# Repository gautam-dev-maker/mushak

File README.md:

# About The Project

Mushak is a micromouse maze solving bot. The aim of this project is to make India's first and smallest half-size micromouse bot. "Mushak" in hindi means "Mouse".

This micromouse consist of a very small coreless motors (6 mm width and 10 mm length) and PCB as it's base . Since coreless motors doesn't provide enough torque for the movements of bot we used gear box to increase the torque.

Mushak is of size 45.7mm x 40.0 mm, which is smaller than similar micromouse using STM32F405RG. We boast of least area consuming micromouse made using STM32 LQFP64 package chips.

|             |  |
:-------------------------:|:-------------------------:

# Table of Content
- [About The Project](#about-the-project)
- [Table of Content](#table-of-content)
- [File Structure](#file-structure)
- [PCB Design](#pcb-design)
    - [Major components used in the PCB include -](#major-components-used-in-the-pcb-include--)
  - [IR sensors](#ir-sensors)
    - [Placement of IR Sensors](#placement-of-ir-sensors)
  - [Power Distribution](#power-distribution)
  - [STM32F405RG (Microcontroller)](#stm32f405rg-microcontroller)
  - [DRV8833 (Motor Driver)](#drv8833-motor-driver)
  - [VL6180X (ToF Sensor)](#vl6180x-tof-sensor)
  - [HC-08 (BLE Module)](#hc-08-ble-module)
  - [AS5600 (Magnetic Encoder)](#as5600-magnetic-encoder)
  - [MPU6500 (IMU)](#mpu6500-imu)
  - [Routing](#routing)
  - [Solutions to some of the major problems faced while designing PCB](#solutions-to-some-of-the-major-problems-faced-while-designing-pcb)
- [CAD Design](#cad-design)
  - [Part Descriptions](#part-descriptions)
  - [Issues Faced in Mechanical Designing](#issues-faced-in-mechanical-designing)
    - [Designing Mount](#designing-mount)
    - [Finalising and Meshing the gears](#finalising-and-meshing-the-gears)
- [Firmware](#firmware)
  - [File Structure](#file-structure-1)
  - [Pinout of STM32F405RG](#pinout-of-stm32f405rg)
    - [Communication Buses](#communication-buses)
    - [ADC](#adc)
    - [PWM](#pwm)
    - [GPIO](#gpio)
  - [How To Use The Firmware](#how-to-use-the-firmware)
    - [Install gcc-arm-none-eabi compiler tool suite](#install-gcc-arm-none-eabi-compiler-tool-suite)
    - [Install ST-Link Toolchain](#install-st-link-toolchain)
    - [Build the source code](#build-the-source-code)
    - [Flash on the STM32 device](#flash-on-the-stm32-device)
- [Resources](#resources)
- [Acknowledgements](#acknowledgements)
- [License](#license)

# File Structure

    .
    ├── Assets             # Documentation files screenshots, gifs, videos of results
    ├── firmware           # contains required code for controlling the bot
    ├── pcb_design         # PCB files made in  kicad 6
    ├── cad_design         # CAD files of mushak (micromouse)
    ├── LICENSE            # License for this project
    └── README.md          # Contains documentation and information about this project

Further file structure of each folder is given in below sections.

# PCB Design

The Mushak PCB design is made on the latest version of KiCAD 6.

Mushak is designed over STM32F405RG microcontroller accomodated with various sensors and drivers for the micromouse.

We designed the smallest micromouse that is based on STM32F405RG microcontroller

### Major components used in the PCB include -

|     Components        |          Description          |
| --------------------- | ----------------------------- |
| STM32F405RG           | Microcontroller |
| VL6180x | ToF sensor4 |
| DRV8833 | Motor Driver |
| MPU6500 | IMU |
| SFH-4045N | Infrared Emitter |
| SFH-3015-FA | Phototransistor (Reciever) |

---

## IR sensors

* The IR sensors include majorly two components, IR emitter which emits the Infrared light of a particular wavelength which is not visible with the human eye. 

* This light gets reflected back from the obstacle present in form of the robot to the photo transistor, when the Infrared light of this perticular wavelength enters the phototransistor device it allows the current to flow from the collector to the emmiter of device. This current flow creates a voltage drop across the resistor connected with the photo transistor and this voltage drop is read by th ADC of the microcontroller which varies as the intensity of light reflected changes. By this way we can determine how far is the obstacle from the robot.

* For controlling the intensity of the transmitted light we used N-Channel Mosfet whose gate is controlled by PWM signal given by the microcontroller.
By varying the PWM duty cycle we can control the intensity of the transmitted light from IR emmiter by which we can control the distance sensitivity.

* Four Sensor pairs are being used in Mushak (Micromouse)

### Placement of IR Sensors

Placing IR sensors pose a challenge, and required rigorous testing and brain storming. 

As can be seen in the image above we have visualised 2 cell based maze and bot is placed in first cell.

* `IR1` (blue rays) is pointing to the left mid point of next cell.
* `IR2` (orange rays) is pointing to the left end of current cell.
* `IR3` (pink rays) is pointing to the right end of current cell.
* `IR4` (green rays) is pointing to the right end of current cell.

To move the bot in straight line along the diagonal maze pattern , we have considered `point 1` and `point 2`. These two points are the edges of diagonal ends of above pattern . So if bot had to move diagonally we can check for readings at these two points and control the bot accordingly.

---

## Power Distribution
* Power to the control circuits is provided by 3V linear Regulator(LDO) which can provide upto 1A current. Power to the motor is directly given to the motor driver through battery.
* Additional capacitors are added across outputs for filtering out the voltage. Voltage divider resistors are being used to monitor the battery voltage. Power indication LED has been provided in the PCB. The input voltage for the PCB is 3.7 voltage through a general LiPo battery.

--- 

## STM32F405RG (Microcontroller)

The below image shows the pinout of STM32F405RG that we will be using for this project :

Decoupling capacitors of 0.1uF are connected near the vdd pins of STM32. Additional external low and high frequency oscillators are added for precise timing.

- HSE(High Speed External) clock - 25 Mhz
- LSE(Low Speed External) clock - 32.769 Khz

Filter circuit is being used for filtering out the analog reference voltage. Additional Debug switches are being added for debugging purposes

---
## DRV8833 (Motor Driver)

* We have used H-bridge motor driver which can control two motors at the same time via PWM (pulse width modulation) from the STM32F405RG (microcontroller).

* The motor driver can supply 1.5 Amps of current per motor which is enough to power up the coreless motors. 

* This motor driver keeps the controls terminals from the microcontrolller isolated from noise and high volatages of the motor power supply.

---

## VL6180X (ToF Sensor)

* We added a Time of Flight sensor in front of the robot to measure the distance of the obstacle in front from the robot.

* This sensor measures the time taken by the light signal to get reflected from the obstacle and then measures the distace of the obstacle from the robot.

* The sensor uses I2C protocol for communication with the microcontroller and send the distance values. It also has an additional feature of sensing the ambeint light which we can use to avoid the problems faced with IR sensors due to varing ambient light conditions.
* Due to cost issues it is not feasible to replace IR sensors with VL6180x, else it could have been a replacement.

---

## HC-08 (BLE Module)

* We used a BLE(Bluetooth Low Energy) module to communicate to the robot. It is one of the most important modules that is being used in mushak, this bluetooth module will enable us to communicate with the robot and precisely tune it to solve the mazes, additionally it makes debugging easier for us making Mushak user friendly.

* The module consumes very less power(since it works on BLE) and works on UART communication to talk with the microcontroller.

* For attaching this module we have provided the JST connectors to connect this module externally when required.

---

## AS5600 (Magnetic Encoder)

* To measure the RPM and the distance that the robot has covered we needed a type of encoder feedback. For this we used AS5600 magnetic encoders to measure the amount of rotation of the robot wheel.

* The magnetic encoders are mounted in an innovative way due to which no external mounts were required for their placement. Since magnets need to be right infront of the IC of AS5600 to get proper reading, we have taken extra care with mount size and shaft placement.

* The sensor works on I2C communication protocol to provide the reading to the microcontroller.

---

## MPU6500 (IMU)

* This sensor gives the feedback of orientaion of the robot. This MEMS based chip has in-built Acclereometer and Gyroscope by which it can determine its orietation with respect to space.

* This sensor works on SPI as well as I2C communication protocol but in our case to get the fastest data transfer, we used use SPI communcation.

---

## Routing

* Front Copper Layer:

* Back Copper Layer:

* Final Routing:

For routing of the control circuitry we used traces of 0.2mm width and for power connections we used 0.4mm width tracks to ensure fairly high current flow.

## Solutions to some of the major problems faced while designing PCB

1) Minimalising passive components is a really hard task. So to solve this I properly reffered the application notes and datasheet of stm32f405RG. Moreover the design is well tested on simulation platform.

2) Efficient placement of components to reduce the size of the PCB. Innovative design to fix sensors and encoders in such a small space.

3) Since IRs are sensitive to ambient light we required a mechanism to adjust the brighness of IR Emitter. So to do that we used a mosfet based circuit, so brightness can be controlled using PWM.

4) It was a big challenge to place 90+ SMD and THT components on a small size PCB of just 45.7x40mm size.

# CAD Design

CAD design consist of 3D modeling of Bot design.Before design can be made on PCB, we need to check if various other aspects of systems and mechanical design satisfy our requiements. So CAD design form a very important part of our project.

## Part Descriptions
* The bot contains a total of 6 main **mechanical** components which are as listed in the following table :

|     Parts             |          Description          |
| --------------------- | ----------------------------- |
| <p align="center">
   | Motors - This motor has </br> dimensions: Length x Dia. 12 x 6 mm and a shaft lenght of 6mm.|
   | Motor_mount - This is the mount for the motors, which holds </br> the motor, shaft, gears, bearing and magnet.Because of less center-to-center distance between gears, after many iterations this mount was designed.|
   | TOF_mount - This is the mount for TOF sensor, which is placed </br> in front. We have used VL6180x TOF sensor.|  
    | IR_mounts - These are the mounts for IR sensors placed </br> at specific angles. SFH-3015-FA and SFH-4045N sensors are phototransistors and IR emitters respectively.|   
    | Gears - The metal gears were extracted from mg90s servos having dimensions: </br> Driving gear:</br> &emsp; &emsp; &emsp;&emsp; &emsp;Teeth 9 </br> &emsp; &emsp; &emsp;&emsp; &emsp;Pressure Angle - 20º</br> &emsp; &emsp; &emsp;&emsp; &emsp;ID - 0.5, OD - 2.14 mm</br> &emsp; &emsp; &emsp;&emsp; &emsp;Width 2.46 mm</br> Driven gear: </br> &emsp; &emsp; &emsp;&emsp; &emsp;Teeth 47 </br> &emsp; &emsp; &emsp;&emsp; &emsp;Pressure Angle 20º</br> &emsp; &emsp; &emsp;&emsp; &emsp;ID - 1.5mm, OD - 9.55 mm</br> &emsp; &emsp; &emsp;&emsp; &emsp; Width 1.2 mm.</br> Center to center distance is 5.80mm and modulus 0.195</br>| 
    | Bearings, shaft and Wheels - These are the passive components used.</br> Bearings x4 of dimensions: ID x OD 1.5 x 4 mm.</br> Shaft x2 of dimensions: Length x Dia. 15 x 1.5 mm.</br> Wheels with dimensions: ID x OD 1.5 x 12.5 mm.</br> A combination of 2 bearings is used to house the shaft for better stability and lesser Vibrations.|
</p>

**NOTE** : 
* ID is abbreviation for Internal Diameter.
* OD is abbreviation for Outer Diameter.

## Issues Faced in Mechanical Designing 
### Designing Mount 
  
* **Issue** : The main issues faced in designing the Mount were As the Gears acquired were of a smaller diameter, there was an issue of interference between the bearing and the motor. As they were too close, it was impossible to 3D print a mount with the thickness less than 1mm.
* **Solution** : The solution opted for this was to actually disalign the motor and the shaft to give room the bearing housing to be 3D printed. This enabled us to print a more stable base due to the stronger Shaft housing.
Below images demonstrate how it was done.

|             |  |  |  |
:-------------------------:|:-------------------------:|:-------------------------:|:-------------------------:
  
### Finalising and Meshing the gears
  
* **Issue** : As there are a varieties of gears available. It was hard for us to choose the right combination and Built the Model and mounts around it.
* **Solution** : We started with finalising the sizes and the gear ratios needed according to the available spaces. We then did the market research to find the gears closest to our needs and incorporated those models into the Design.

<p align="center">

# Firmware

The firmware for this project is written using STM32-HAL. STM32 HAL consist of bare-metal register address and light weight peripheral libraries giving programmer the full control. For running multiple tasks we are using [FreeRTOS](https://www.freertos.org). We will be storing the maze in flash memory, since page size is 2 bytes, we need to access 2 bytes at a a time. 

The firmware is required to interact with the following external sensors/peripherals: 

- [SFH-4045N](https://dammedia.osram.info/media/resource/hires/osram-dam-2496064/SFH%204045N.pdf) : Infrared Emitter for detecting walls.
- [SFH-3015-FA](https://dammedia.osram.info/media/resource/hires/osram-dam-2495986/SFH%203015%20FA.pdf) : Infrared Receiver to receive the emitted 
- [AS5600-ASOT](https://ams.com/documents/20143/36005/AS5600_DS000365_5-00.pdf) : Encoders to calculate the movements of wheel.
- [DRV8833](https://www.ti.com/lit/ds/slvsar1e/slvsar1e.pdf?ts=1661677330657&ref_url=https%253A%252F%252Fwww.google.com%252F) : Dual H-bridge Motor driver required to control motor.
- [MPU6500](https://invensense.tdk.com/wp-content/uploads/2020/06/PS-MPU-6500A-01-v1.3.pdf) : Gyroscope and Accelerometer sensor.
- [SMT-0440-S-R](https://www.puiaudio.com/media/SpecSheet/SMT-0440-S-R.pdf) : buzzer to generate the victory sound.
- [VL6180x](https://www.st.com/resource/en/datasheet/vl6180x.pdf) : Time of flight sensor to measure the distance between wall and bot.
- [HC-08](http://www.hc01.com/downloads/HC-08A%20version%20english%20datasheet.pdf) : Bluetooth module primarily used for logging. It uses 9600 baud rate for communication.

## File Structure

    .
    ├── Firmware                                # contains required code for controlling the bot
    │    ├── Core                               # Contains developer code for sensors and other peripherals
    │    │   ├── As5600                         # Driver Api for AS5600
    │    │   │   ├── as5600.c                   # Source code for AS5600
    │    │   │   └── as5600.h                   # Header file for AS5600
    │    │   ├── Ble_logger                     # Bluetooth logger API using UART
    │    │   │   ├── ble_logger.c               # Bluetooth logger source code
    │    │   │   └── ble_logger.h               # Bluetooth logger header file
    │    │   ├── Drv8833                        # Code for Motor Control
    │    │   │   ├── drv8833.c                  # Source code for DRV8833
    │    │   │   └── drv8833.h                  # Header files for DRV8833
    │    │   ├── Inc                  
    │    │   │   ├── FreeRTOSConfig.h           # FreeRTOS configuration file
    │    │   │   ├── main.h                     # Main header file
    │    │   │   ├── stm32f4xx_hal_conf.h       # STM32 HAL configuration file
    │    │   │   └── stm32f4xx_it.h             # contains header of interrupt handlers
    │    │   ├── Mpu6500
    │    │   │   ├── mpu6500.c                  # Source code for MPU6500 Driver
    │    │   │   └── mpu6500.h                  # Header file for MPU6500 Driver
    │    │   ├── Peripheral                     
    │    │   │   └── I2c                        # I2C API's handler
    │    │   ├── Src
    │    │   │   ├── freertos.c                 # FreeRTOS source code
    │    │   │   ├── main.c                     # Main source code
    │    │   │   ├── stm32f4xx_hal_msp.c        # MSP initialisation and deinitialiation source code
    │    │   │   ├── stm32f4xx_it.c             # source code for interrupt handlers
    │    │   │   └── system_stm32f4xx.c         # CSMSIS peripheral device layer source code
    │    │   └── Vl6180x
    │    │       ├── vl6180x.c                  # VL6180x Driver source code
    │    │       └── vl6180x.h                  # VL6180x header file
    │    ├── Drivers                            # STM32 Driver Code involving bare metal registers
    │    ├── Middlewares                        # FreeRTOS APIs for scheduling algorithm
    │    ├── node_modules                       # HTML modules for viewing STM32 HAL API documentation
    │    ├── Makefile                           # Automake compilation instructions
    │    ├── STM32F411CEUx_FLASH.ld             # Linker script for compilation   
    └────└── node_modules                       # HTML modules for viewing STM32 HAL API

## Pinout of STM32F405RG

The below image shows the pinout of STM32F405RG that we will be using for this project :

### Communication Buses

- **I2C (Inter-Integrated Circuit)** : We use two encoders(*AS5600*),so we needed to use two different I2C bus. *Vl6180x* (ToF) sensor also uses I2C bus communication, so overall 3 I2C bus communication is used.
- **SPI (serial peripheral interface)** : *MPU6500* supports both I2C as well as SPI, but since SPI offers faster communication , we decided to go with it.
- **UART (Universal Asynchronous Receiver/Transmitter)**: *HC-08* bluetooth module , which will be used for logging functions on UART transmission protocol.

### ADC

- SFH-3015-FA (IR receiver) gives analog signals, so it requires ADC module to read the readings. So we require 4 ADC channels for reading IR sensors
- To measure voltage level of battery one ADC channel will be required

So overall 5 ADC channels are required.

### PWM

- DRV8833 (Dual H-bridge Motor Driver) requires 4 PWM channel.
- To control the brightness of 4 SFH-4045N (IR emitter) we need 4 more PWM channels
- To generate noise in the buzzer we will need 1 more PWM channel.

So in overall we will require 9 PWM channels.

### GPIO

- 2 GPIOs are required for 2 LEDs
- 1 GPIOs are required for 1 Button

so In overall 3 GPIO pins are used for getting input and output.

## How To Use The Firmware

### Install gcc-arm-none-eabi compiler tool suite

* ### For Linux 

```
sudo apt-get update
sudo apt-get install -y gcc-arm-none-eabi
```

* ### For MacOS
```
brew tap ArmMbed/homebrew-formulae
brew install arm-none-eabi-gcc
```
### Install ST-Link Toolchain

* ST-Link toolchain is required for flashing on STM32 chip.

* ### For Linux
```
sudo apt-get update
sudo apt-get -y install stlink-tools
```

* ### For MacOS

```
brew install stlink
```

### Build the source code

* ### Clone the reponsitory and change the directory to firmware

```
git clone https://github.com/gautam-dev-maker/mushak.git
cd mushak/firmware
```

* ### Build using make tool
```
make -j4  # based on no. of logical cores available in your system
```

### Flash on the STM32 device

```
make flash  # Currently only st-link support is added
```

# Resources
* [Project Futura](http://micromouseusa.com/?page_id=1342) is a tutorial for micromouse designing
* [Micromouse Tyre](http://micromouseusa.com/?page_id=1342) a blog related how to select the tyres for micromouse
* [Phase-lead controller](https://micromouseonline.com/2011/05/16/designing-a-phase-lead-controller/) an alternative to PID control systems for micromouse.
* [Slip Compensation](https://robotics.stackexchange.com/questions/1658/implementing-slip-compensation-into-a-half-size-micromouse) discussion on how to compensate slip in micromouse which becomes a serious issue
* [Kerise v5](https://github.com/kerikun11/micromouse-kerise-v5) Smallest micromouse ever made, contains good documentation of design,pcb and code.
* [SolidWorks Tutorial](https://www.youtube.com/watch?v=Ulttc_2p4DY&list=PLrOFa8sDv6jcp8E3ayUFZ4iNI8uuPjXHe) to sharpen your skills in SolidWorks.

# Acknowledgements
* [SRA VJTI](http://sravjti.in) for providing us with required resources and support.
* [Ryotaro Onuki](https://github.com/kerikun11) for helping with all the designs and technical aspect of micromouse. His willingness to share his experience and answering our question has led to the start of the project.

# License
The [License](https://github.com/gautam-dev-maker/mushak/blob/master/LICENSE) Used for this Project.

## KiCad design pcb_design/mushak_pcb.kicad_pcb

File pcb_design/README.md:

# PCB Design

The Mushak PCB design is made on the latest version of KiCAD 6.

Mushak is designed over STM32F405RG microcontroller accomodated eith various sensors and drivers for the micromouse.

We designed the smallest micromouse that is based on STM32F405RG microcontroller

### Major components used in the PCB include -

- STM32F405RG - Microcontroller
- VL6180x - ToF sensor4
- DRV8833 - Motor Driver
- MPU6500 - IMU
- SFH-4045N - Infrared Emitter
- SFH-3015-FA - Phototransistor (Reciever)

---

## IR sensors

The IR sensors include majorly two components, IR emitter which emits the Infrared light of a perticular wavelength which is not visible with the human eye. 

This light gets reflected back from the obstacle present in fromt of the robot to the photo transistor, when the Infrared light of this perticular wavelength enters the phototransistor device it allows the current to flow from the collector to the emmiter of device. This current flow creates a voltage drop across the resistor connected with the photo transistor and this voltage drop is read by th ADC of the microcontroller which varies as the intensity of light reflected changes. By this way we can determine how far is the obstacle from the robot.

For controlling the intensity of the transmitted light we used N-Channel Mosfet whose gate is controlled by PWM signal given by the microcontroller.
By varying the PWM duty cycle we can control the intensity of the transmitted light from IR emmiter by which we can control the distance sensitivity.

4 Sensor pairs are being used in Mushak (Micromouse)

---

## Power Distribution
Power to the control circuits is provided by 3V linear Regulator(LDO) which can provide upto 1A current. Power to the motor is directly given to the motor driver through battery.
Additional capacitors are added across outputs for filtering out the voltage. Voltage divider resistors are being used to monitor the battery voltage. Power indication LED has been provided in the PCB. The input voltage for the PCB is 3.7 voltage through a general LiPo battery.

--- 

## STM32F405RG (Microcontroller)

The below image shows the pinout of STM32F405RG that we will be using for this project :

Decoupling capacitors of 0.1uF are connected near the vdd pins of STM32. Additional external low and high frequency oscillators are added for precise timing.

- HSE(High Speed External) clock - 25 Mhz
- LSE(Low Speed External) clock - 32.769 Khz

Filter circuit is being used for filtering out the analog reference voltage. Additional Debug switches are being added for debugging purposes

---
## DRV8833 (Motor Driver)

We have used H-bridge motor driver which can control two motors at the same time via PWM (pulse width modulation) from the STM32F405RG (microcontroller).

The motor driver can supply 1.5 Amps of current per motor which is enough to power up the coreless motors. 

This motor driver keeps the controls terminals from the microcontrolller isolated from noise and high volatages of the motor power supply.

---

## VL6180X (ToF Sensor)

We added a Time of Flight sensor in front of the robot to measure the distance of the obstacle in front from the robot.

This sensor measures the time taken by the light signal to get reflected from the obstacle and then measures the distace of the obstacle from the robot.

The sensor uses I2C protocol for communication with the microcontroller and send the distance values. It also has an additional feature of sensing the ambeint light which we can use to avoid the problems faced with IR sensors due to varing ambient light conditions.

---

## HC-08 (BLE Module)

We used a BLE(Bluetooth Low Energy) module to talk to the robot. It is one of the most important modules that is being used in mushak, this bluetooth module will eanble us to talk with the robot and precisely tune it to solve the mazes, additionally it makes debugging easier for us making Mushak user friendly.

The module consumes very less power and works on UART communication to talk with the microcontroller.

For attaching this module we have provided the JST connectors to connect this module externally when required.

---

## AS5600 (Magnetic Encoder)

To measure the RPM and teh distance that the robot has covered we needed a type of encoder feedback. For this we used AS5600 magnetic encoders to measure the amount of rotation of the robot wheel.

The magnetic encoders are mounted in an innovative way due to which no external mounts were required for their placement.

The sensor works on I2C communication protocol to provide the feedback to the microcontroller.

---

## MPU6500 (IMU)

This sensor gives the feedback of orientaion of the robot. This MEMS based chip has in-built Acclereometer and Gyroscope by which it can determine its orietation with respect to space.

This sensor works on SPI as well as I2C communication protocol but in our case to get the fastest data transfer, we used use SPI communcation.

---

## Routing

Front Copper Layer:

Back Copper Layer:

Final Routing:

For routing of the control circuitry we used traces of 0.2mm width and for power connections we used 0.4mm width tracks to ensure fairly high current flow.

These are some images of the routing done on Mushak -
## Solutions to some of the major problems faced while designing PCB

1) Minimalising passive components is a really hard task. So to solve this I properly reffered the application notes and datasheet of stm32f405RG. Moreover the design is well tested on simulation platform.

2) Efficient placement of components to reduce the size of the PCB. Innovative design to fix sensors and encoders in such a small space.

3) Since IRs are sensitive to ambient light we required a mechanism to adjust the brighness of IR Emitter. So to do that we used a mosfet based circuit, so brightness can be controlled using PWM.

4) It was a big challenge to place 90+ SMD and THT components on a small size PCB of just 45.7x40mm size.

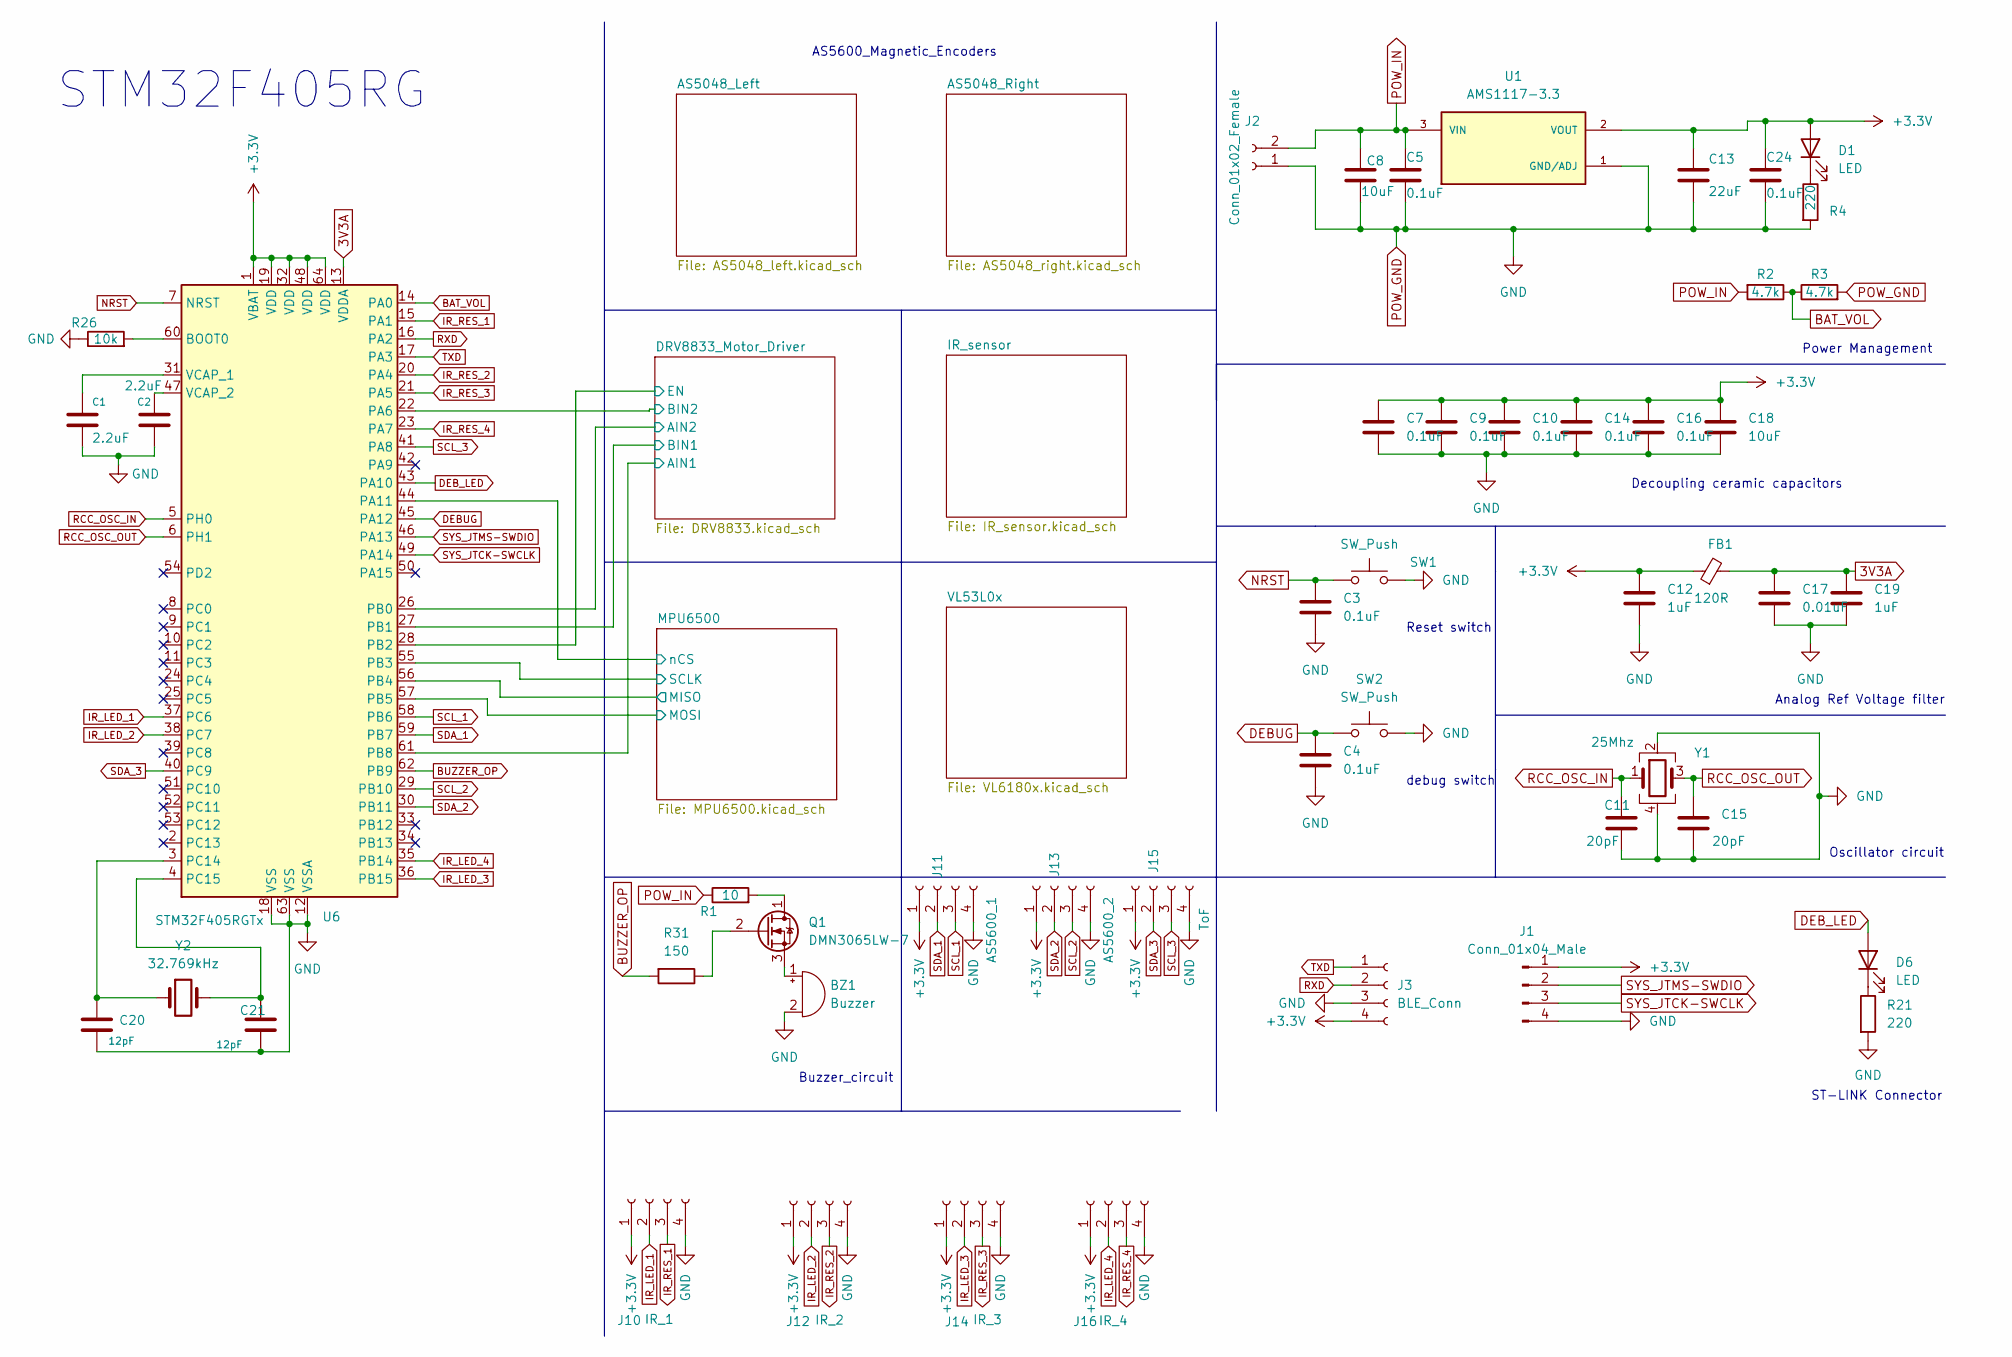
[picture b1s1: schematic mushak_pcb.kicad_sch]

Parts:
BZ1: Buzzer; XDCR_SMT-0440-T-R
C1, C2: 2.2uF; C_0603_1608Metric
C3, C4, C5, C7, C9, C10, C14, C16, C24: 0.1uF; C_0402_1005Metric
C8, C18: 10uF; C_0603_1608Metric
C11, C15: 20pF; C_0402_1005Metric
C12, C19: 1uF; C_0603_1608Metric
C13: 22uF; C_0603_1608Metric
C17: 0.01uF; C_0402_1005Metric
C20, C21: 12pF; C_0402_1005Metric
D1, D6: LED; LED_0402_1005Metric
FB1: 120R; L_0805_2012Metric
J1: Conn_01x04_Male; JST_SH_BM04B-SRSS-TB_1x04-1MP_P1.00mm_Vertical
J2: Conn_01x02_Female; JST_EH_B2B-EH-A_1x02_P2.50mm_Vertical
J3: BLE_Conn; JST_SH_BM04B-SRSS-TB_1x04-1MP_P1.00mm_Vertical
J10: IR_1; IR_HOST_V_04
J11: AS5600_1; STAND_HOST_04
J12: IR_2; IR_HOST_V_04
J13: AS5600_2; STAND_HOST_04
J14: IR_3; IR_HOST_V_04
J15: ToF; STAND_HOST_04
J16: IR_4; IR_HOST_V_04
Q1: DMN3065LW-7; SOT-323_SC-70
R1: 10; R_0603_1608Metric
R2, R3: 4.7k; R_0402_1005Metric
R4, R21: 220; R_0603_1608Metric
R26: 10k; R_0402_1005Metric
R31: 150; R_0402_1005Metric
SW1, SW2: SW_Push; SW_TL1015AF160QG
U1: AMS1117-3.3; SOT229P700X180-4N; PARTREV N/A
U6: STM32F405RGTx; LQFP-64_10x10mm_P0.5mm
Y1: 25Mhz; Crystal_SMD_3225-4Pin_3.2x2.5mm
Y2: 32.769kHz; XTAL_ABS07-32.768KHZ-T

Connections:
3V3A: C17.1, C19.1, FB1.2, U6.13 (VDDA)
+3.3V: C7.1, C9.1, C10.1, C12.1, C13.1, C14.1, C16.1, C18.1, C24.1, D1.2 (A), FB1.1, J1.1, J3.4, J10.1, J11.1, J12.1, J13.1, J14.1, J15.1, J16.1, U1.2 (VOUT), U6.1 (VBAT), U6.19 (VDD), U6.32 (VDD), U6.48 (VDD), U6.64 (VDD); also elsewhere on the board
/DRV8833_Motor_Driver/AIN1: U6.61 (PB8); also elsewhere on the board
/DRV8833_Motor_Driver/AIN2: U6.26 (PB0); also elsewhere on the board
/DRV8833_Motor_Driver/BIN1: U6.27 (PB1); also elsewhere on the board
/DRV8833_Motor_Driver/BIN2: U6.22 (PA6); also elsewhere on the board
/DRV8833_Motor_Driver/EN: U6.28 (PB2); also elsewhere on the board
/MPU6500/MISO: U6.56 (PB4); also elsewhere on the board
/MPU6500/MOSI: U6.57 (PB5); also elsewhere on the board
/MPU6500/SCLK: U6.55 (PB3); also elsewhere on the board
/MPU6500/nCS: U6.44 (PA11); also elsewhere on the board
BAT_VOL: R2.1, R3.1, U6.14 (PA0)
BUZZER_OP: R31.2, U6.62 (PB9)
DEBUG: C4.1, SW2.1, U6.45 (PA12)
DEB_LED: D6.2 (A), U6.43 (PA10)
IR_LED_1: J10.2, U6.37 (PC6)
IR_LED_2: J12.2, U6.38 (PC7)
IR_LED_3: J14.2, U6.36 (PB15)
IR_LED_4: J16.2, U6.35 (PB14)
IR_RES_1: J10.3, U6.15 (PA1)
IR_RES_2: J12.3, U6.20 (PA4)
IR_RES_3: J14.3, U6.21 (PA5)
IR_RES_4: J16.3, U6.23 (PA7)
NRST: C3.1, SW1.1, U6.7 (NRST)
unnamed: BZ1.1 (-), Q1.3 (S)
unnamed: C1.1, U6.31 (VCAP_1)
unnamed: C2.1, U6.47 (VCAP_2)
unnamed: C20.1, U6.3 (PC14), Y2.1
unnamed: C21.1, U6.4 (PC15), Y2.2
unnamed: D1.1 (K), R4.1
unnamed: D6.1 (K), R21.1
unnamed: Q1.1 (D), R1.2
unnamed: Q1.2 (G), R31.1
unnamed: R26.2, U6.60 (BOOT0)
POW_GND: BZ1.2 (+), C1.2, C2.2, C3.2, C4.2, C5.2, C7.2, C8.2, C9.2, C10.2, C11.2, C12.2, C13.2, C14.2, C15.2, C16.2, C17.2, C18.2, C19.2, C20.2, C21.2, C24.2, J1.4, J2.1, J3.3, J10.4, J11.4, J12.4, J13.4, J14.4, J15.4, J16.4, R3.2, R4.2, R21.2, R26.1, SW1.2, SW2.2, U1.1 (GND/ADJ), U6.12 (VSSA), U6.18 (VSS), U6.63 (VSS), Y1.2, Y1.4; also elsewhere on the board
POW_IN: C5.1, C8.1, J2.2, R1.1, R2.2, U1.3 (VIN); also elsewhere on the board
RCC_OSC_IN: C11.1, U6.5 (PH0), Y1.1
RCC_OSC_OUT: C15.1, U6.6 (PH1), Y1.3
RXD: J3.2, U6.16 (PA2)
SCL_1: J11.3, U6.58 (PB6)
SCL_2: J13.3, U6.29 (PB10)
SCL_3: J15.3, U6.41 (PA8)
SDA_1: J11.2, U6.59 (PB7)
SDA_2: J13.2, U6.30 (PB11)
SDA_3: J15.2, U6.40 (PC9)
SYS_JTCK-SWCLK: J1.3, U6.49 (PA14)
SYS_JTMS-SWDIO: J1.2, U6.46 (PA13)
TXD: J3.1, U6.17 (PA3)

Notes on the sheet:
Power Management
debug switch
Decoupling ceramic capacitors
ST-LINK Connector
Analog Ref Voltage filter
Buzzer_circuit
Reset switch
AS5600_Magnetic_Encoders
STM32F405RG
Oscillator circuit

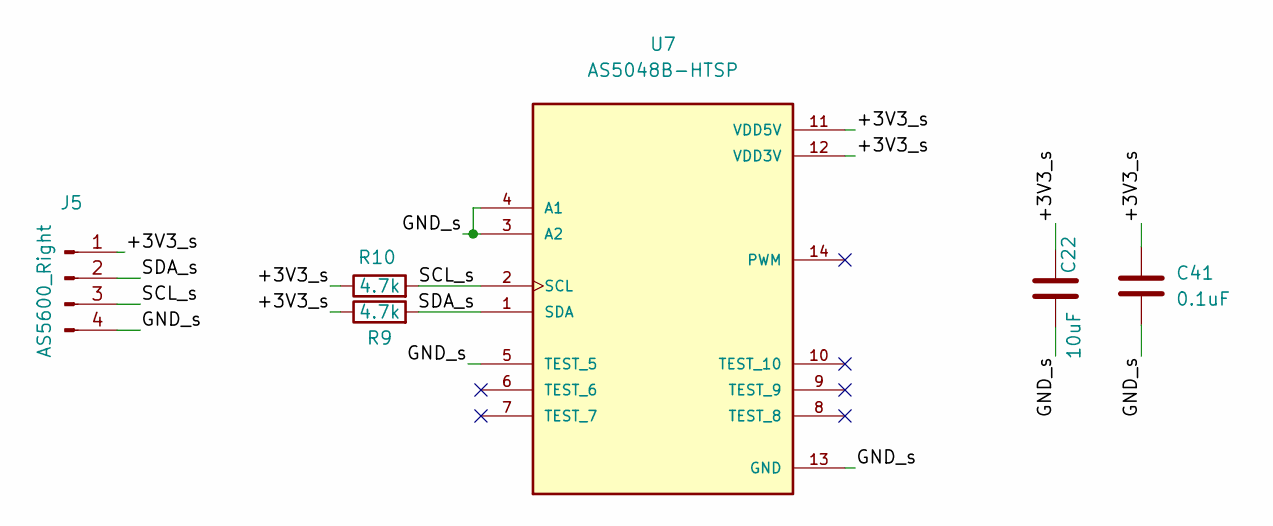
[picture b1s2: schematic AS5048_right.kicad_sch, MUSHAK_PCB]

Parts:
C22: 10uF; C_0603_1608Metric
C41: 0.1uF; C_0402_1005Metric
J5: AS5600_Right; STAND_SLAVE_04
R9, R10: 4.7k; R_0402_1005Metric
U7: AS5048B-HTSP; SOP65P640X120-14N; PARTREV 1-11

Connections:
/AS5048_Right/+3V3_s: C22.2, C41.1, J5.1, R9.1, R10.1, U7.11 (VDD5V), U7.12 (VDD3V)
/AS5048_Right/GND_s: C22.1, C41.2, J5.4, U7.3 (A2), U7.4 (A1), U7.5 (TEST_5), U7.13 (GND)
/AS5048_Right/SCL_s: J5.3, R10.2, U7.2 (SCL)
/AS5048_Right/SDA_s: J5.2, R9.2, U7.1 (SDA)

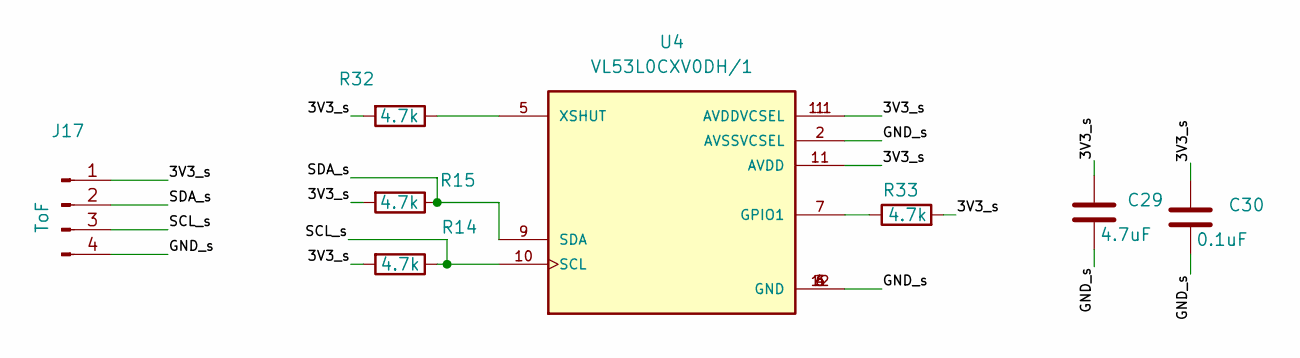
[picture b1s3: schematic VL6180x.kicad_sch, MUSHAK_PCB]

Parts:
C29: 4.7uF; C_0603_1608Metric
C30: 0.1uF; C_0402_1005Metric
J17: ToF; STAND_SLAVE_04
R14, R15, R32, R33: 4.7k; R_0402_1005Metric
U4: VL53L0CXV0DH/1; XDCR_VL53L0CXV0DH_1

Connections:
/VL53L0x/3V3_s: C29.1, C30.1, J17.1, R14.2, R15.2, R32.2, R33.2, U4.1 (AVDDVCSEL), U4.1.1 (AVDDVCSEL), U4.11 (AVDD)
/VL53L0x/GND_s: C29.2, C30.2, J17.4, U4.2 (AVSSVCSEL), U4.3 (GND), U4.4 (GND), U4.6 (GND), U4.12 (GND)
/VL53L0x/SCL_s: J17.3, R14.1, U4.10 (SCL)
/VL53L0x/SDA_s: J17.2, R15.1, U4.9 (SDA)
unnamed: R32.1, U4.5 (XSHUT)
unnamed: R33.1, U4.7 (GPIO1)

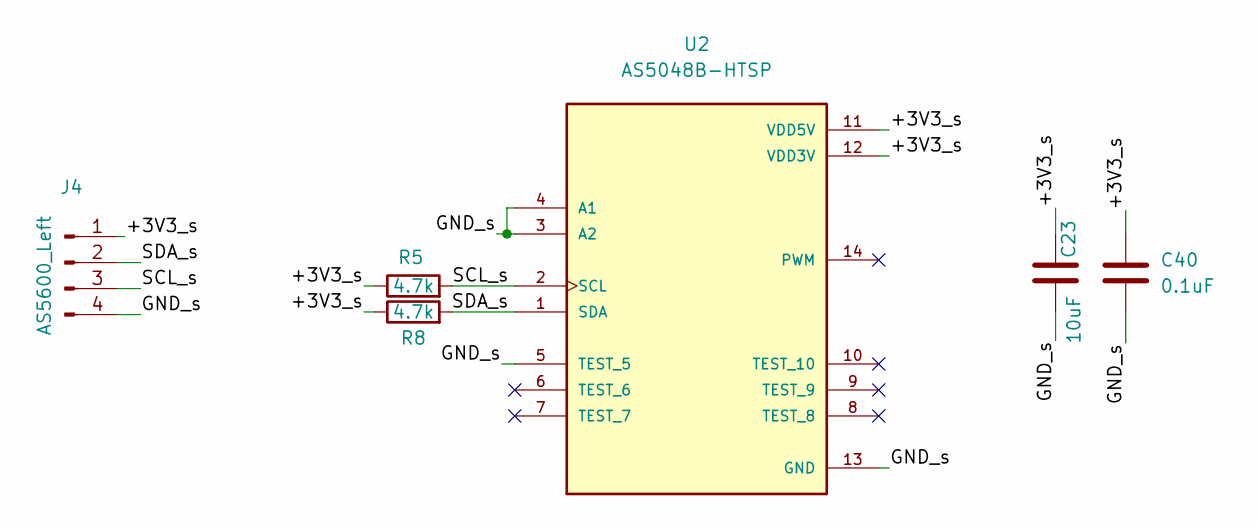
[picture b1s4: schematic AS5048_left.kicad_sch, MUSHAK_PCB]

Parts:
C23: 10uF; C_0603_1608Metric
C40: 0.1uF; C_0402_1005Metric
J4: AS5600_Left; STAND_SLAVE_04
R5, R8: 4.7k; R_0402_1005Metric
U2: AS5048B-HTSP; SOP65P640X120-14N; PARTREV 1-11

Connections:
/AS5048_Left/+3V3_s: C23.2, C40.1, J4.1, R5.1, R8.1, U2.11 (VDD5V), U2.12 (VDD3V)
/AS5048_Left/GND_s: C23.1, C40.2, J4.4, U2.3 (A2), U2.4 (A1), U2.5 (TEST_5), U2.13 (GND)
/AS5048_Left/SCL_s: J4.3, R5.2, U2.2 (SCL)
/AS5048_Left/SDA_s: J4.2, R8.2, U2.1 (SDA)

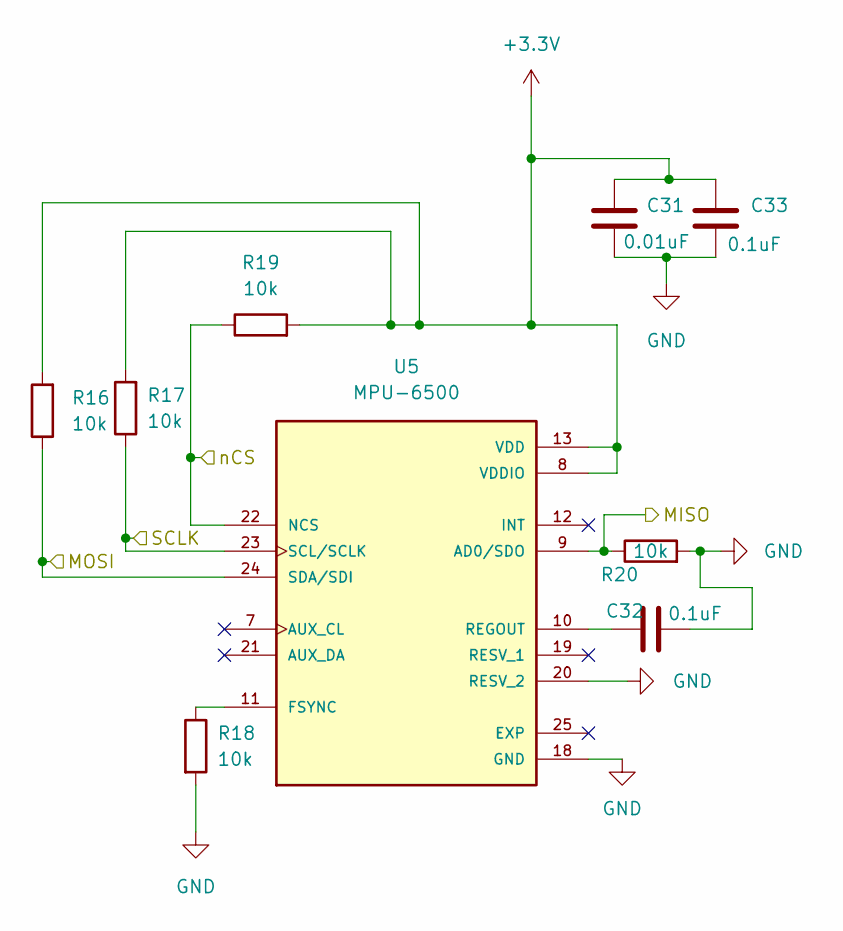
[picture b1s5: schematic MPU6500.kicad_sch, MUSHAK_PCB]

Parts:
C31: 0.01uF; C_0402_1005Metric
C32, C33: 0.1uF; C_0402_1005Metric
R16, R17, R18, R19, R20: 10k; R_0402_1005Metric
U5: MPU-6500; QFN40P300X300X95-25N; PARTREV 1.3

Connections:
+3.3V: C31.1, C33.1, R16.2, R17.2, R19.2, U5.8 (VDDIO), U5.13 (VDD); also elsewhere on the board
/MPU6500/MISO: R20.1, U5.9 (AD0/SDO); also elsewhere on the board
/MPU6500/MOSI: R16.1, U5.24 (SDA/SDI); also elsewhere on the board
/MPU6500/SCLK: R17.1, U5.23 (SCL/SCLK); also elsewhere on the board
/MPU6500/nCS: R19.1, U5.22 (NCS); also elsewhere on the board
unnamed: C32.2, U5.10 (REGOUT)
unnamed: R18.1, U5.11 (FSYNC)
POW_GND: C31.2, C32.1, C33.2, R18.2, R20.2, U5.18 (GND), U5.20 (RESV_2); also elsewhere on the board

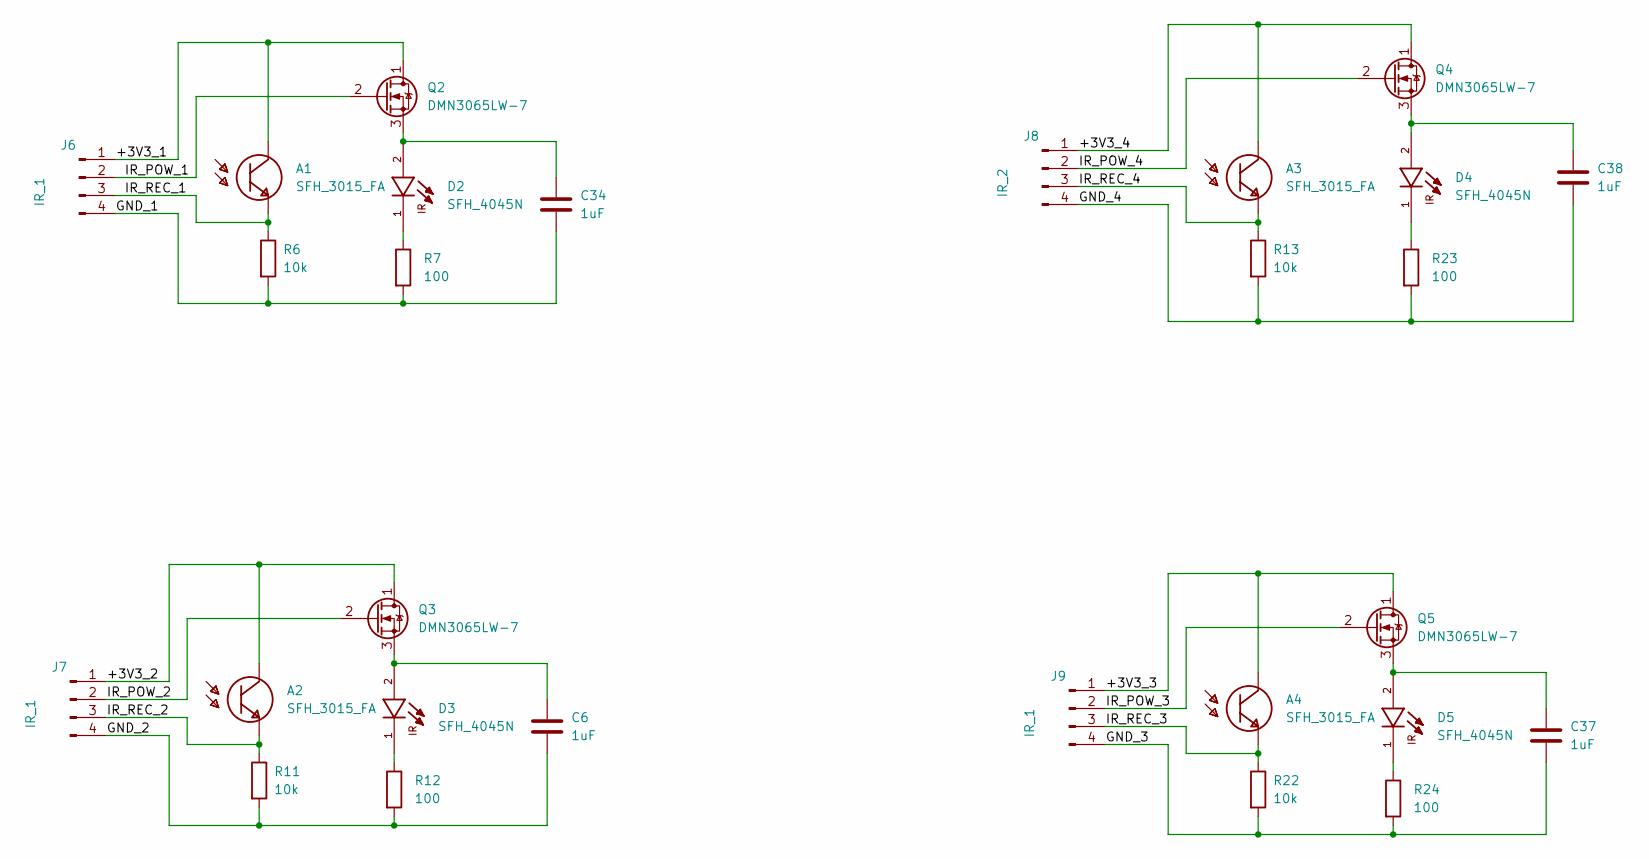
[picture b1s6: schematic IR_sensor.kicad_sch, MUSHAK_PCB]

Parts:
A1, A2, A3, A4: SFH_3015_FA; XDCR_SFH_3015_FA; PARTREV 1.6
C6, C34, C37, C38: 1uF; C_0603_1608Metric
D2, D3, D4, D5: SFH_4045N; LED_SFH_4045N; PARTREV 1.5
J6, J7, J9: IR_1; IR_SLAVE_V_04
J8: IR_2; IR_SLAVE_V_04
Q2, Q3, Q4, Q5: DMN3065LW-7; SOT-323_SC-70
R6, R11, R13, R22: 10k; R_0402_1005Metric
R7, R12, R23, R24: 100; R_0603_1608Metric

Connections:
/IR_sensor/+3V3_1: A1.2, J6.1, Q2.1 (D)
/IR_sensor/+3V3_2: A2.2, J7.1, Q3.1 (D)
/IR_sensor/+3V3_3: A4.2, J9.1, Q5.1 (D)
/IR_sensor/+3V3_4: A3.2, J8.1, Q4.1 (D)
/IR_sensor/GND_1: C34.2, J6.4, R6.2, R7.2
/IR_sensor/GND_2: C6.2, J7.4, R11.2, R12.2
/IR_sensor/GND_3: C37.2, J9.4, R22.2, R24.2
/IR_sensor/GND_4: C38.2, J8.4, R13.2, R23.2
/IR_sensor/IR_POW_1: J6.2, Q2.2 (G)
/IR_sensor/IR_POW_2: J7.2, Q3.2 (G)
/IR_sensor/IR_POW_3: J9.2, Q5.2 (G)
/IR_sensor/IR_POW_4: J8.2, Q4.2 (G)
/IR_sensor/IR_REC_1: A1.1, J6.3, R6.1
/IR_sensor/IR_REC_2: A2.1, J7.3, R11.1
/IR_sensor/IR_REC_3: A4.1, J9.3, R22.1
/IR_sensor/IR_REC_4: A3.1, J8.3, R13.1
unnamed: C6.1, D3.2, Q3.3 (S)
unnamed: C34.1, D2.2, Q2.3 (S)
unnamed: C37.1, D5.2, Q5.3 (S)
unnamed: C38.1, D4.2, Q4.3 (S)
unnamed: D2.1, R7.1
unnamed: D3.1, R12.1
unnamed: D4.1, R23.1
unnamed: D5.1, R24.1

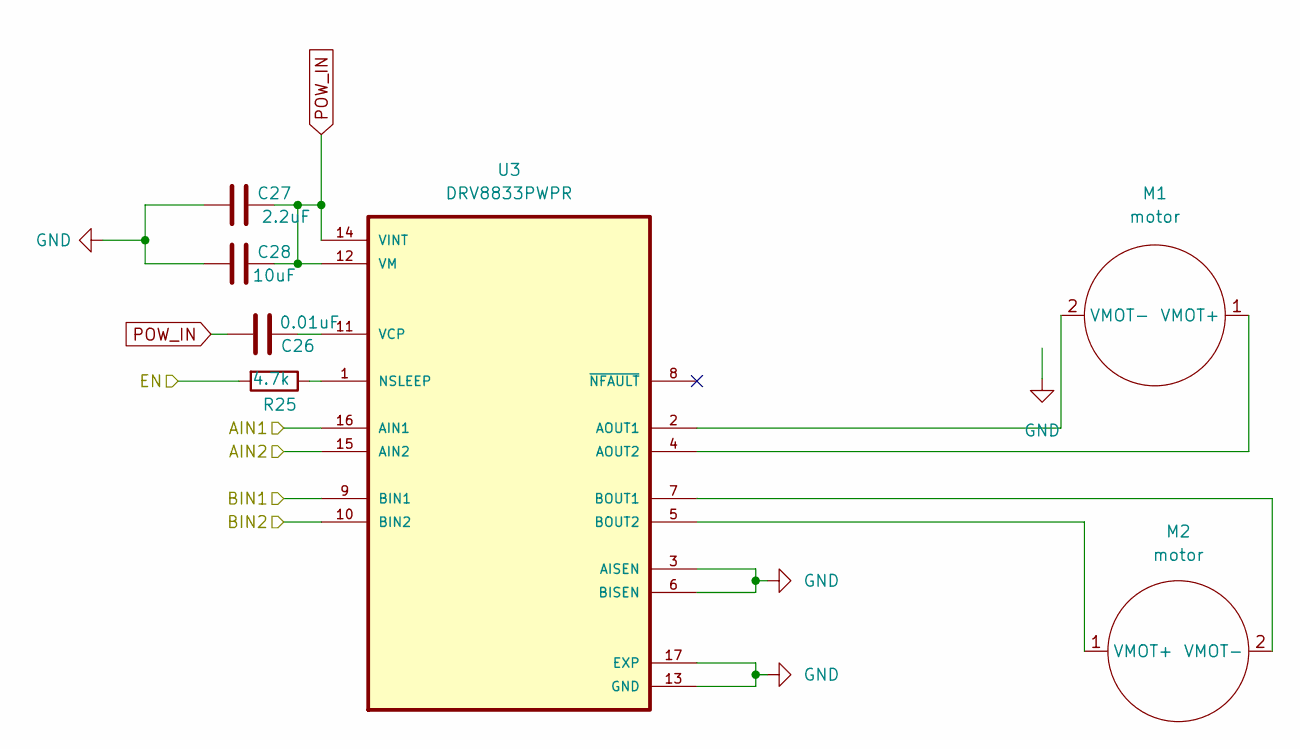
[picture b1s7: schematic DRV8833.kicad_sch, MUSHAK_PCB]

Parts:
C26: 0.01uF; C_0402_1005Metric
C27: 2.2uF; C_0603_1608Metric
C28: 10uF; C_0603_1608Metric
M1, M2: motor
R25: 4.7k; R_0402_1005Metric
U3: DRV8833PWPR; IC_DRV8833PWPR; PARTREV E

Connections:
/DRV8833_Motor_Driver/AIN1: U3.16 (AIN1); also elsewhere on the board
/DRV8833_Motor_Driver/AIN2: U3.15 (AIN2); also elsewhere on the board
/DRV8833_Motor_Driver/BIN1: U3.9 (BIN1); also elsewhere on the board
/DRV8833_Motor_Driver/BIN2: U3.10 (BIN2); also elsewhere on the board
/DRV8833_Motor_Driver/EN: R25.2; also elsewhere on the board
unnamed: C26.2, U3.11 (VCP)
unnamed: M1.1 (VMOT+), U3.4 (AOUT2)
unnamed: M1.2 (VMOT-), U3.2 (AOUT1)
unnamed: M2.1 (VMOT+), U3.5 (BOUT2)
unnamed: M2.2 (VMOT-), U3.7 (BOUT1)
unnamed: R25.1, U3.1 (NSLEEP)
POW_GND: C27.1, C28.1, U3.3 (AISEN), U3.6 (BISEN), U3.13 (GND), U3.17 (EXP); also elsewhere on the board
POW_IN: C26.1, C27.2, C28.2, U3.12 (VM), U3.14 (VINT); also elsewhere on the board
